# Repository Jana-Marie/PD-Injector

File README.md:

# PD-Injector

This is a USB power delivery Power/Data injector. It has PCB USB-C input sockets and one output plug, the data lines from one input and the power lines from the other are combined and present at the output. Therefore you can have a data connection from your (not PD capable) computer, while having power from a power supply. 

The PCB should be ordered with a thickness of 0.6mm so the on PCB sockets fits USB-C cables. For the USB-C plug, any Board Edge connector should work e.g. Molex 1054440001

Please be aware that DP Alt mode does not work as it requires the CC lines which are routed to the PD supply.

#### This repo is forked from the PD Buddy Wye.
[https://git.clarahobbs.com/pd-buddy/pd-buddy-wye](https://git.clarahobbs.com/pd-buddy/pd-buddy-wye)

Original README:

## PD Buddy Wye

Power/data splitter for PD Buddy Sink.

This PCB must be 0.6 mm thick so the USB Type-C card edge receptacles work.
Copper thickness can be 1 or 2 oz, ENIG finish preferred.

The PCB is made with [KiCad][], so you'll need that if you want to make any
changes.  Several PCB fabricators accept KiCad PCB files directly now, but if
you intend to order from one that does not, you'll need KiCad to plot the
Gerbers.

KiCad 4 supports loading footprint libraries from Git repositories, but its
support for doing the same with symbol libraries is lacking.  To address this,
I added the variable `_KI_LIB_GIT`.  Set this path in the main KiCad window
(Preferences > Configure Paths) to point to a local copy of the
[kicad-library][] repository to ensure that you're using the latest schematic
libraries.

[KiCad]: http://kicad-pcb.org/
[kicad-library]: https://github.com/KiCad/kicad-library/

### License

PD Buddy Wye is Copyright (C) 2017-2018 Clara G. Hobbs, and made available
under the CERN Open Hardware Licence v1.2.  See LICENSE for more information.

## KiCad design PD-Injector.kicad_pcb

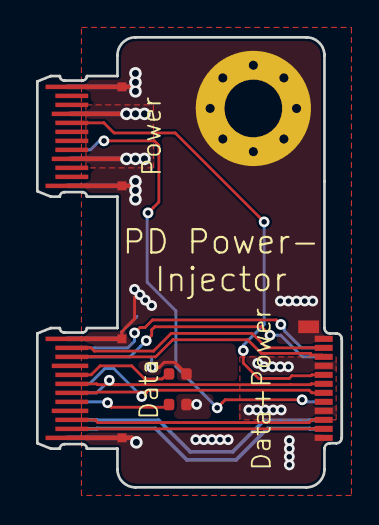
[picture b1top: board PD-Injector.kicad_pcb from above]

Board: 2 copper layers, 16.9 x 25.0 mm, 6 parts (0 on the bottom side), 16 nets.

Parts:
J1: Power; USB_C_Receptacle_PCBEdge_Alt_ShieldPads
J2: UFP; USB_C_Receptacle_PCBEdge_Alt_ShieldPads
MK1: M3; MountingHole_3.2mm_M3_Pad_Via
P1: DFP+Power; USB_C_Plug_Molex_105444
R1, R2: 5.1k; R_0402_1005Metric

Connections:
/CC1D: J2.A5, R1.1
/CC1P: J1.A5, P1.A5
/CC2D: J2.B5, R2.2
/CC2P: J1.B5, P1.B5
/D+: J2.A6, J2.B6, P1.A6
/D-: J2.A7, J2.B7, P1.A7
/RX1+: J2.B11, P1.B11
/RX1-: J2.B10, P1.B10
/RX2+: J2.A11, P1.A11
/RX2-: J2.A10, P1.A10
/TX1+: J2.A2, P1.A2
/TX1-: J2.A3, P1.A3
/TX2+: J2.B2, P1.B2
/TX2-: J2.B3, P1.B3
GND: J1.A1, J1.A12, J1.B1, J1.B12, J1.S1, J2.A1, J2.A12, J2.B1, J2.B12, J2.S1, MK1.1, P1.A1, P1.A12, P1.B1, P1.B12, P1.S1, R1.2, R2.1
VBUS: J1.A4, J1.A9, J1.B4, J1.B9, J2.A4, J2.A9, J2.B4, J2.B9, P1.A4, P1.A9, P1.B4, P1.B9

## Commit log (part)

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2019-02-16 added files
2019-02-18 added Images
2019-02-18 added CAD files
2019-02-19 updated design
2021-11-07 Update README.md
    https://forum.kicad.info/t/warning-avoid-all-links-to-kicad-pcb-org-use-kicad-org/31521
